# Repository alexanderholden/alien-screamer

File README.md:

This is my reconstruction of the Alien Screamer PCB from the schematic.
I did not design any of the schematics, just the PCB.
All credit to Ray Wilson
https://musicfromouterspace.com/analogsynth_new/ALIENSCREAMER/ALIENSCREAMER.php

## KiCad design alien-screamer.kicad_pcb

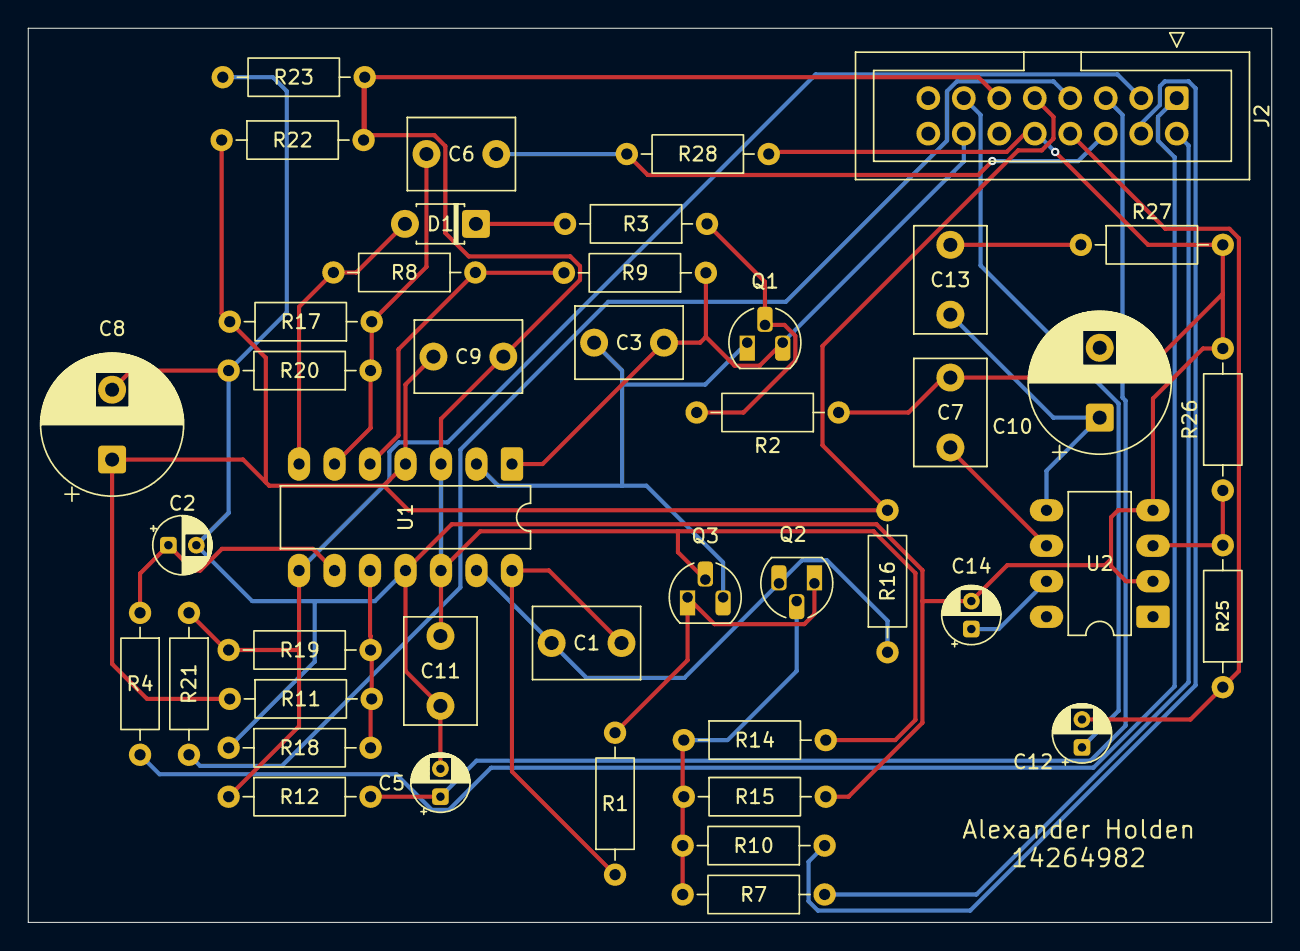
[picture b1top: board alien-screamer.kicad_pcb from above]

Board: 2 copper layers, 89.0 x 64.0 mm, 44 parts (0 on the bottom side), 30 nets.

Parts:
C1: 100p; C_Disc_D7.5mm_W5.0mm_P5.00mm
C2, C5, C12: 1u; CP_Radial_D4.0mm_P2.00mm
C3: .001u; C_Disc_D7.5mm_W5.0mm_P5.00mm
C6: .01u; C_Disc_D7.5mm_W5.0mm_P5.00mm
C7, C9, C11: .1u; C_Disc_D7.5mm_W5.0mm_P5.00mm
C8: 470u; CP_Radial_D10.0mm_P5.00mm
C10: 220u; CP_Radial_D10.0mm_P5.00mm
C13: .047u; C_Disc_D7.5mm_W5.0mm_P5.00mm
C14: 10u; CP_Radial_D4.0mm_P2.00mm
D1: D; D_T-1_P5.08mm_Horizontal
J2: Conn_02x08_Odd_Even; IDC-Header_2x08_P2.54mm_Vertical
Q1: 2N5457; TO-92_HandSolder
Q2, Q3: 2N3904; TO-92_HandSolder
R1, R3, R9, R17: 10K; R_Axial_DIN0207_L6.3mm_D2.5mm_P10.16mm_Horizontal
R2, R16: 2M; R_Axial_DIN0207_L6.3mm_D2.5mm_P10.16mm_Horizontal
R4: 3K; R_Axial_DIN0207_L6.3mm_D2.5mm_P10.16mm_Horizontal
R7, R11, R18, R19, R25, R28: 100K; R_Axial_DIN0207_L6.3mm_D2.5mm_P10.16mm_Horizontal
R8: 300K; R_Axial_DIN0207_L6.3mm_D2.5mm_P10.16mm_Horizontal
R10, R12: 75K; R_Axial_DIN0207_L6.3mm_D2.5mm_P10.16mm_Horizontal
R14: 2K; R_Axial_DIN0207_L6.3mm_D2.5mm_P10.16mm_Horizontal
R15: 220k; R_Axial_DIN0207_L6.3mm_D2.5mm_P10.16mm_Horizontal
R20: 15K; R_Axial_DIN0207_L6.3mm_D2.5mm_P10.16mm_Horizontal
R21, R22, R23, R26: 4.7K; R_Axial_DIN0207_L6.3mm_D2.5mm_P10.16mm_Horizontal
R27: 10; R_Axial_DIN0207_L6.3mm_D2.5mm_P10.16mm_Horizontal
U1: LM324; DIP-14_W7.62mm_LongPads
U2: LM386; DIP-8_W7.62mm_LongPads

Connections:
/BN: C2.2, C5.2, C7.2, C8.2, C11.2, C14.2, J2.BN (Pin_10), R2.1, R15.2, R18.1, R20.2, R23.2, R26.2, R27.2, R28.1, U1.11 (V-), U2.2 (-), U2.4 (GND)
/BP: C8.1, C9.1, J2.BP (Pin_9), R11.1, R16.2, R17.2, R22.1, U1.4 (V+)
/X1: J2.X1 (Pin_1), R4.2
/X2: J2.X2 (Pin_2), R7.1
/X3: J2.X3 (Pin_3), R12.1, R19.2, R21.1, U1.8
/X4: J2.X4 (Pin_4), R10.1
/X5: C5.1, J2.X5 (Pin_5), R12.2
/X6: C6.1, J2.X6 (Pin_6), R28.2
/X7: J2.X7 (Pin_7), R21.2
/X8: C12.2, J2.X8 (Pin_8), R25.1
/X13: C12.1, J2.X13 (Pin_13)
/X14: C3.2, J2.X14 (Pin_14), Q1.3 (S), R9.1, U1.1
GND: C9.2, C11.1, J2.GND (Pin_11), Q3.2 (B), R14.2, R22.2, R23.1, U1.3 (+), U1.12 (+)
unnamed: C1.2, R1.1, U1.14
unnamed: C10.1, C13.1, U2.5
unnamed: C13.2, R27.1
unnamed: D1.2 (A), R8.2, U1.7
unnamed: D1.1 (K), R3.2
unnamed: C3.1, Q1.1 (D), Q3.3 (C), U1.2 (-)
unnamed: Q1.2 (G), R2.2, R3.1
unnamed: Q2.2 (B), R7.2, R10.2, R14.1, R15.1
unnamed: C1.1, Q2.3 (C), R16.1, U1.13 (-)
unnamed: Q2.1 (E), Q3.1 (E), R1.2
unnamed: R8.1, R9.2, U1.5 (+)
unnamed: C6.2, R17.1, R20.1, U1.6 (-)
unnamed: R11.2, R18.2, R19.1, U1.10 (+)
unnamed: C2.1, R4.1, U1.9 (-)
unnamed: R25.2, R26.1, U2.3 (+)
unnamed: C14.1, U2.7 (BYPASS)
unnamed: C7.1, U2.6 (V+)

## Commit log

2026-02-26 Finished PCB, experimenting with connectors - unsure if it will work but have sent off PCB design for fabrication
